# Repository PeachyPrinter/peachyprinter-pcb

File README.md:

If you're looking for the version of the Peachy Printer that we were gearing up to manufacture, look at mini-v1.14. 

If you're wondering what v1.15 is all about, it's a work-in-progress that we started because of a huge panic: right around the time we were getting ready for our final test manufacturing run, the STM32F042 practically vanished from the entire supply chain! We couldn't find them anywhere! So I quickly started redoing the board to use an STM32F070 instead, but in the end the supply chain recovered before we had to pull the trigger on the respin.

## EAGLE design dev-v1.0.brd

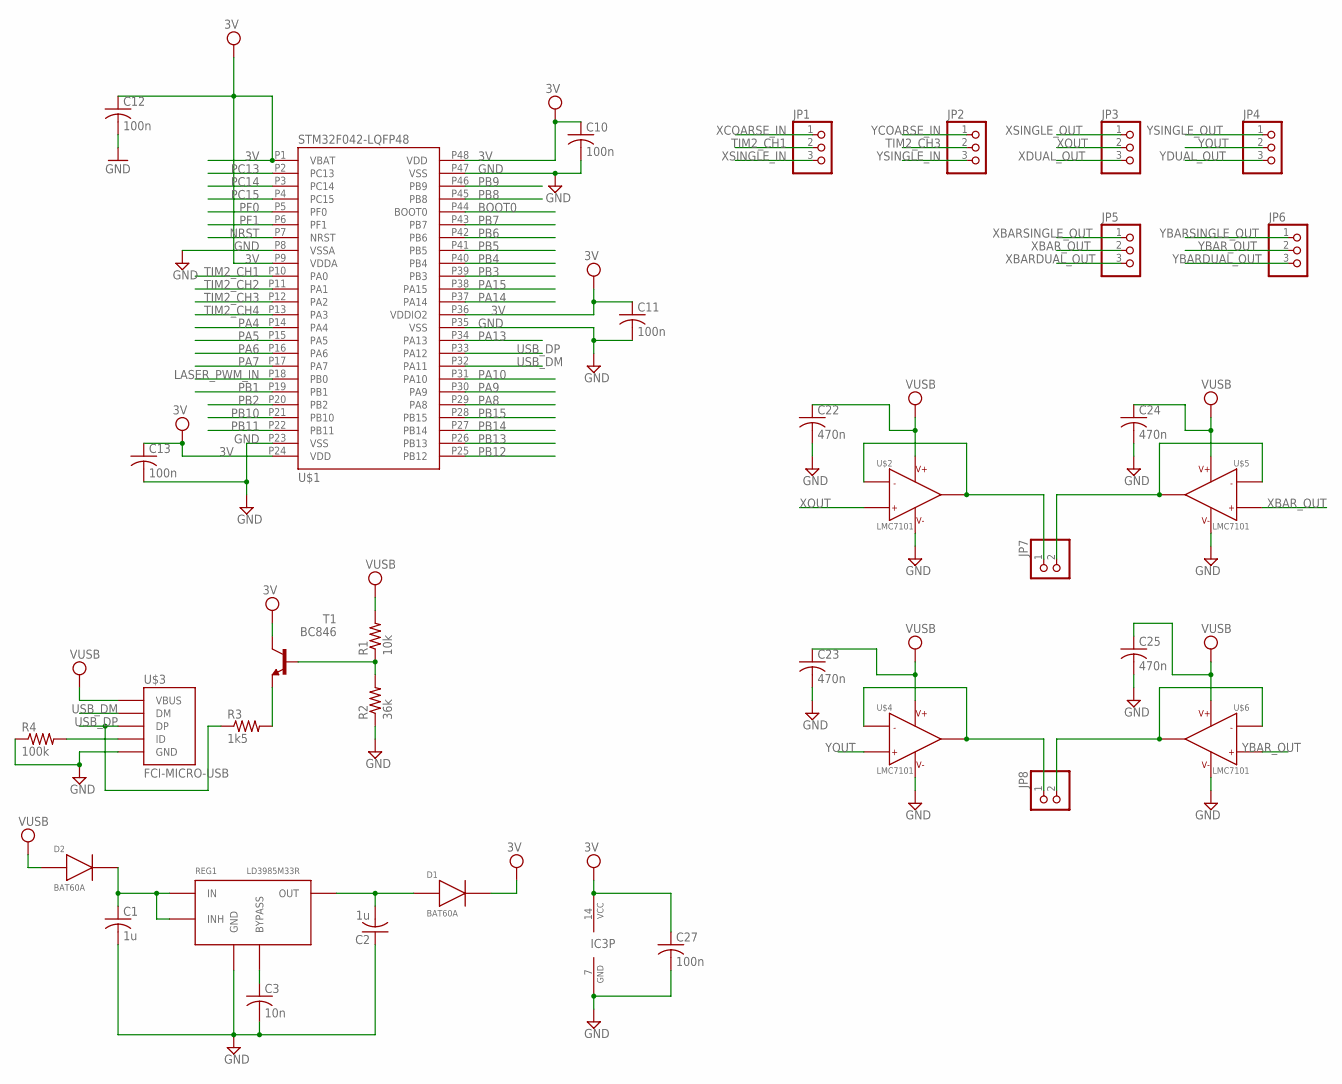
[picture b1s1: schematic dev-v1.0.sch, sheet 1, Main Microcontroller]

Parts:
C1, C2: 1u; C0603
C3: 10n; C0603
C10, C11, C12, C13, C27: 100n; C0603
C22, C23, C24, C25: 470n; C0603
D1, D2: BAT60A; SOD323
IC3: 74S04D; SO14
JP1, JP2, JP3, JP4, JP5, JP6: PINHD-1X3; 1X03
JP7, JP8: PINHD-1X2; 1X02
R1: 10k; R0603
R2: 36k; R0603
R3: 1k5; R0603
R4: 100k; R0603
REG1: LD3985M33R; SOT23-5L
T1: BC846; SOT23
U$1: STM32F042-LQFP48; LQFP48
U$2, U$4, U$5, U$6: LMC7101; SOT23-5
U$3: FCI-MICRO-USB; FCI-MICROUSB

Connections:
3V: C10.1, C11.1, C12.1, C13.1, C27.1, D1.1, IC3.14 (VCC), T1.3 (C), U$1.P1 (VBAT), U$1.P9 (VDDA), U$1.P24 (VDD), U$1.P36 (VDDIO2), U$1.P48 (VDD); also elsewhere on the board
3V3: C2.2, D1.2, REG1.OUT
BOOT0: U$1.P44 (BOOT0); also elsewhere on the board
GND: C1.2, C2.1, C3.2, C10.2, C11.2, C12.2, C13.2, C22.2, C23.2, C24.2, C25.2, C27.2, IC3.7 (GND), R2.1, R4.1, REG1.GND, U$1.P8 (VSSA), U$1.P23 (VSS), U$1.P35 (VSS), U$1.P47 (VSS), U$2.5, U$3.P5 (GND), U$4.5, U$5.5, U$6.5; also elsewhere on the board
LASER_PWM_IN: U$1.P18 (PB0); also elsewhere on the board
unnamed: C3.1, REG1.BYPASS
unnamed: R1.1, R2.2, T1.1 (B)
unnamed: R3.2, T1.2 (E)
unnamed: C1.1, D2.1, REG1.IN, REG1.INHIBIT (INH)
unnamed: R4.2, U$3.P4 (ID)
unnamed: JP7.1, U$2.1, U$2.4
unnamed: JP8.1, U$4.1, U$4.4
unnamed: JP7.2, U$5.1, U$5.4
unnamed: JP8.2, U$6.1, U$6.4
NRST: U$1.P7 (NRST); also elsewhere on the board
PA4: U$1.P14 (PA4); also elsewhere on the board
PA5: U$1.P15 (PA5); also elsewhere on the board
PA6: U$1.P16 (PA6); also elsewhere on the board
PA7: U$1.P17 (PA7); also elsewhere on the board
PA8: U$1.P29 (PA8); also elsewhere on the board
PA9: U$1.P30 (PA9); also elsewhere on the board
PA10: U$1.P31 (PA10); also elsewhere on the board
PA13: U$1.P34 (PA13); also elsewhere on the board
PA14: U$1.P37 (PA14); also elsewhere on the board
PA15: U$1.P38 (PA15); also elsewhere on the board
PB1: U$1.P19 (PB1); also elsewhere on the board
PB2: U$1.P20 (PB2); also elsewhere on the board
PB3: U$1.P39 (PB3); also elsewhere on the board
PB4: U$1.P40 (PB4); also elsewhere on the board
PB5: U$1.P41 (PB5); also elsewhere on the board
PB6: U$1.P42 (PB6); also elsewhere on the board
PB7: U$1.P43 (PB7); also elsewhere on the board
PB8: U$1.P45 (PB8); also elsewhere on the board
PB9: U$1.P46 (PB9); also elsewhere on the board
PB10: U$1.P21 (PB10); also elsewhere on the board
PB11: U$1.P22 (PB11); also elsewhere on the board
PB12: U$1.P25 (PB12); also elsewhere on the board
PB13: U$1.P26 (PB13); also elsewhere on the board
PB14: U$1.P27 (PB14); also elsewhere on the board
PB15: U$1.P28 (PB15); also elsewhere on the board
PC13: U$1.P2 (PC13); also elsewhere on the board
PC14: U$1.P3 (PC14); also elsewhere on the board
PC15: U$1.P4 (PC15); also elsewhere on the board
PF0: U$1.P5 (PF0); also elsewhere on the board
PF1: U$1.P6 (PF1); also elsewhere on the board
TIM2_CH1: JP1.2, U$1.P10 (PA0); also elsewhere on the board
TIM2_CH2: U$1.P11 (PA1); also elsewhere on the board
TIM2_CH3: JP2.2, U$1.P12 (PA2); also elsewhere on the board
TIM2_CH4: U$1.P13 (PA3); also elsewhere on the board
USB_DM: U$1.P32 (PA11), U$3.P2 (DM); also elsewhere on the board
USB_DP: R3.1, U$1.P33 (PA12), U$3.P3 (DP); also elsewhere on the board
VUSB: C22.1, C23.1, C24.1, C25.1, D2.2, R1.2, U$2.2, U$3.P1 (VBUS), U$4.2, U$5.2, U$6.2; also elsewhere on the board
XBARDUAL_OUT: JP5.3; also elsewhere on the board
XBARSINGLE_OUT: JP5.1; also elsewhere on the board
XBAR_OUT: JP5.2, U$5.3
XCOARSE_IN: JP1.1; also elsewhere on the board
XDUAL_OUT: JP3.3; also elsewhere on the board
XOUT: JP3.2, U$2.3
XSINGLE_IN: JP1.3; also elsewhere on the board
XSINGLE_OUT: JP3.1; also elsewhere on the board
YBARDUAL_OUT: JP6.3; also elsewhere on the board
YBARSINGLE_OUT: JP6.1; also elsewhere on the board
YBAR_OUT: JP6.2, U$6.3
YCOARSE_IN: JP2.1; also elsewhere on the board
YDUAL_OUT: JP4.3; also elsewhere on the board
YOUT: JP4.2, U$4.3
YSINGLE_IN: JP2.3; also elsewhere on the board
YSINGLE_OUT: JP4.1; also elsewhere on the board

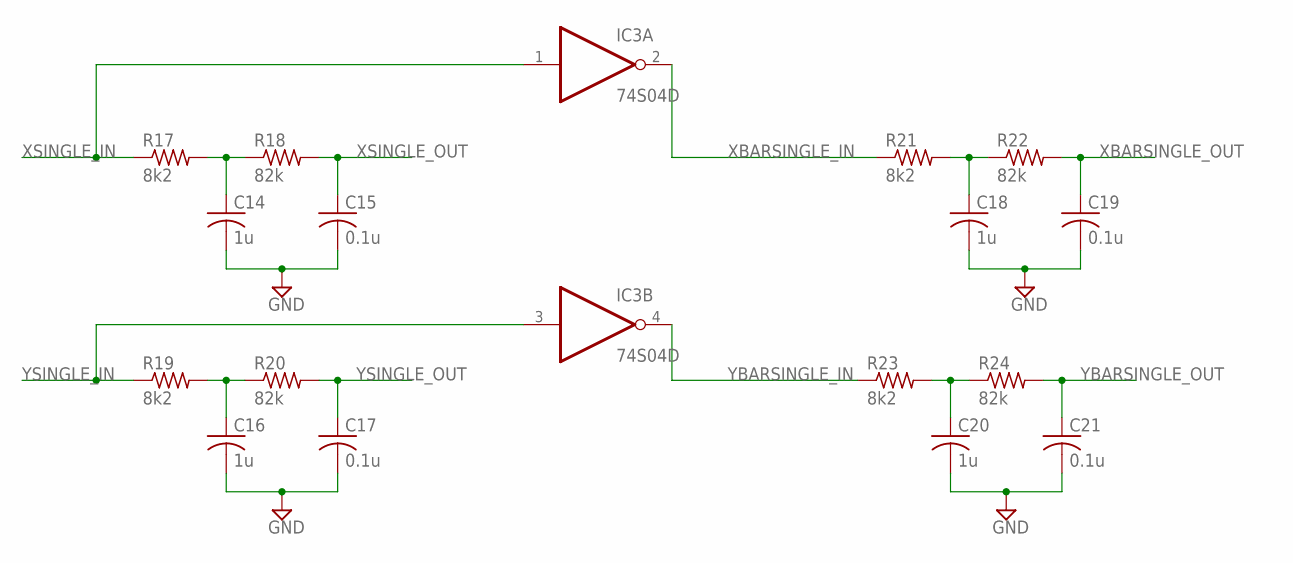
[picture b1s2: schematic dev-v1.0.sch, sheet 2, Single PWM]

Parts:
C14, C16, C18, C20: 1u; C0603
C15, C17, C19, C21: 0.1u; C0603
IC3: 74S04D; SO14
R17, R19, R21, R23: 8k2; R0603
R18, R20, R22, R24: 82k; R0603

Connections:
GND: C14.2, C15.2, C16.2, C17.2, C18.2, C19.2, C20.2, C21.2; also elsewhere on the board
unnamed: C14.1, R17.2, R18.1
unnamed: C16.1, R19.2, R20.1
unnamed: C18.1, R21.2, R22.1
unnamed: C20.1, R23.2, R24.1
XBARSINGLE_IN: IC3.2 (O), R21.1
XBARSINGLE_OUT: C19.1, R22.2; also elsewhere on the board
XSINGLE_IN: IC3.1 (I), R17.1; also elsewhere on the board
XSINGLE_OUT: C15.1, R18.2; also elsewhere on the board
YBARSINGLE_IN: IC3.4 (O), R23.1
YBARSINGLE_OUT: C21.1, R24.2; also elsewhere on the board
YSINGLE_IN: IC3.3 (I), R19.1; also elsewhere on the board
YSINGLE_OUT: C17.1, R20.2; also elsewhere on the board

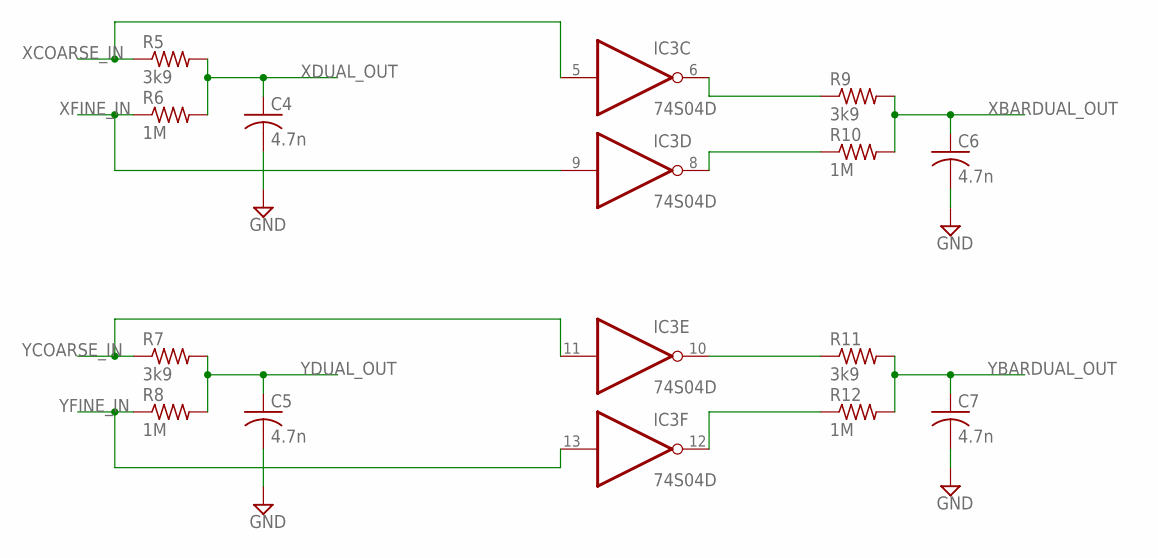
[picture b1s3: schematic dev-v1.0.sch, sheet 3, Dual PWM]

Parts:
C4, C5, C6, C7: 4.7n; C0603
IC3: 74S04D; SO14
R5, R7, R9, R11: 3k9; R0603
R6, R8, R10, R12: 1M; R0603

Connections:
GND: C4.2, C5.2, C6.2, C7.2; also elsewhere on the board
unnamed: IC3.10 (O), R11.1
unnamed: IC3.12 (O), R12.1
unnamed: IC3.8 (O), R10.1
unnamed: IC3.6 (O), R9.1
XBARDUAL_OUT: C6.1, R9.2, R10.2; also elsewhere on the board
XCOARSE_IN: IC3.5 (I), R5.1; also elsewhere on the board
XDUAL_OUT: C4.1, R5.2, R6.2; also elsewhere on the board
XFINE_IN: IC3.9 (I), R6.1
YBARDUAL_OUT: C7.1, R11.2, R12.2; also elsewhere on the board
YCOARSE_IN: IC3.11 (I), R7.1; also elsewhere on the board
YDUAL_OUT: C5.1, R7.2, R8.2; also elsewhere on the board
YFINE_IN: IC3.13 (I), R8.1

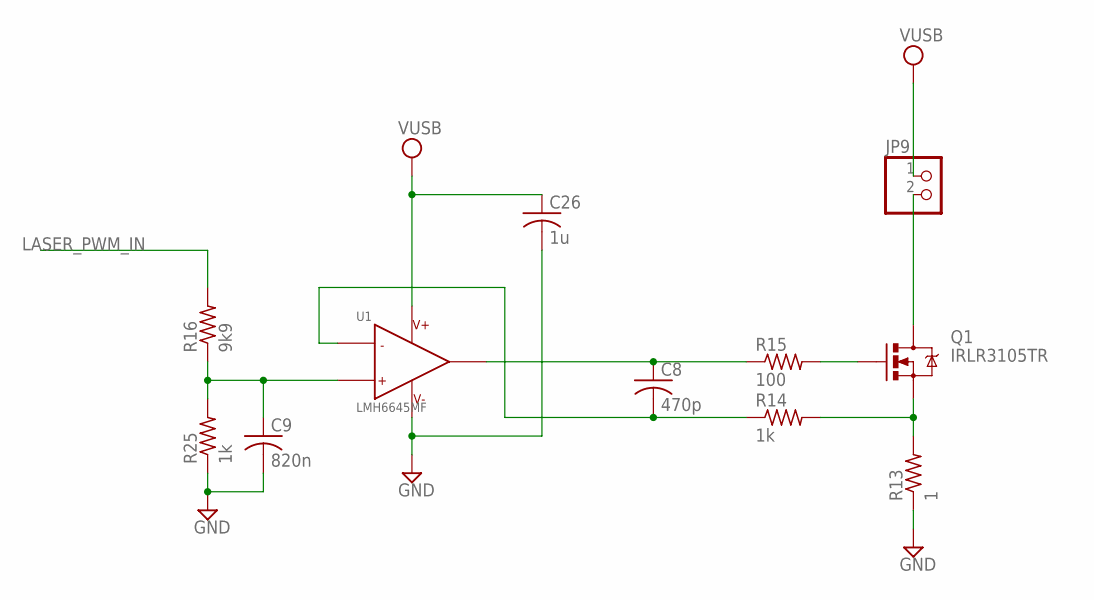
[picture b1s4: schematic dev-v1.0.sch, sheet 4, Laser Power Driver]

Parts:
C8: 470p; C0603
C9: 820n; C0603
C26: 1u; C0603
JP9: PINHD-1X2; 1X02
Q1: IRLR3105TR; DPAK
R13: 1; R0603
R14, R25: 1k; R0603
R15: 100; R0603
R16: 9k9; R0603
U1: LMH6645MF; SOT23-5

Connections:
GND: C9.2, C26.2, R13.1, R25.1, U1.2 (V-); also elsewhere on the board
LASER_PWM_IN: R16.2; also elsewhere on the board
unnamed: JP9.2, Q1.4 (D)
unnamed: Q1.3 (S), R13.2, R14.2
unnamed: C8.2, R14.1, U1.4 (IN-)
unnamed: Q1.1 (G), R15.2
unnamed: C8.1, R15.1, U1.1 (OUT)
unnamed: C9.1, R16.1, R25.2, U1.3 (IN+)
VUSB: C26.1, JP9.1, U1.5 (V+); also elsewhere on the board

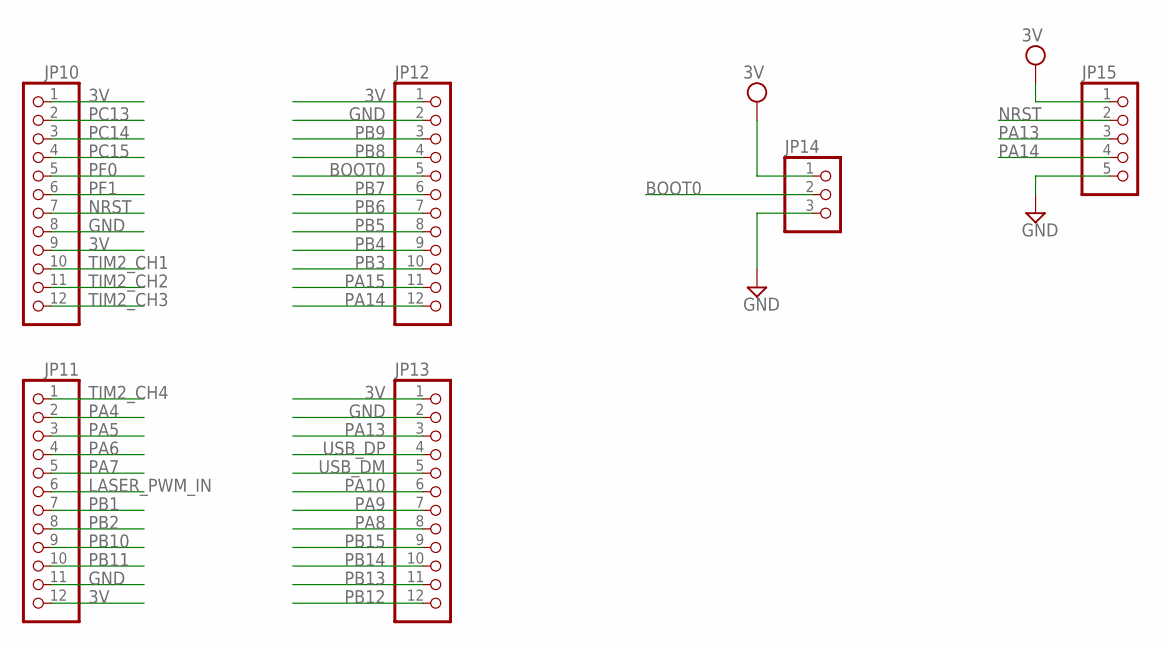
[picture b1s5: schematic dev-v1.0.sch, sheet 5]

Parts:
JP10, JP11, JP12, JP13: PINHD-1X12; 1X12
JP14: PINHD-1X3; 1X03
JP15: PINHD-1X5; 1X05

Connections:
3V: JP10.1, JP10.9, JP11.12, JP12.1, JP13.1, JP14.1, JP15.1; also elsewhere on the board
BOOT0: JP12.5, JP14.2; also elsewhere on the board
GND: JP10.8, JP11.11, JP12.2, JP13.2, JP14.3, JP15.5; also elsewhere on the board
LASER_PWM_IN: JP11.6; also elsewhere on the board
NRST: JP10.7, JP15.2; also elsewhere on the board
PA4: JP11.2; also elsewhere on the board
PA5: JP11.3; also elsewhere on the board
PA6: JP11.4; also elsewhere on the board
PA7: JP11.5; also elsewhere on the board
PA8: JP13.8; also elsewhere on the board
PA9: JP13.7; also elsewhere on the board
PA10: JP13.6; also elsewhere on the board
PA13: JP13.3, JP15.3; also elsewhere on the board
PA14: JP12.12, JP15.4; also elsewhere on the board
PA15: JP12.11; also elsewhere on the board
PB1: JP11.7; also elsewhere on the board
PB2: JP11.8; also elsewhere on the board
PB3: JP12.10; also elsewhere on the board
PB4: JP12.9; also elsewhere on the board
PB5: JP12.8; also elsewhere on the board
PB6: JP12.7; also elsewhere on the board
PB7: JP12.6; also elsewhere on the board
PB8: JP12.4; also elsewhere on the board
PB9: JP12.3; also elsewhere on the board
PB10: JP11.9; also elsewhere on the board
PB11: JP11.10; also elsewhere on the board
PB12: JP13.12; also elsewhere on the board
PB13: JP13.11; also elsewhere on the board
PB14: JP13.10; also elsewhere on the board
PB15: JP13.9; also elsewhere on the board
PC13: JP10.2; also elsewhere on the board
PC14: JP10.3; also elsewhere on the board
PC15: JP10.4; also elsewhere on the board
PF0: JP10.5; also elsewhere on the board
PF1: JP10.6; also elsewhere on the board
TIM2_CH1: JP10.10; also elsewhere on the board
TIM2_CH2: JP10.11; also elsewhere on the board
TIM2_CH3: JP10.12; also elsewhere on the board
TIM2_CH4: JP11.1; also elsewhere on the board
USB_DM: JP13.5; also elsewhere on the board
USB_DP: JP13.4; also elsewhere on the board

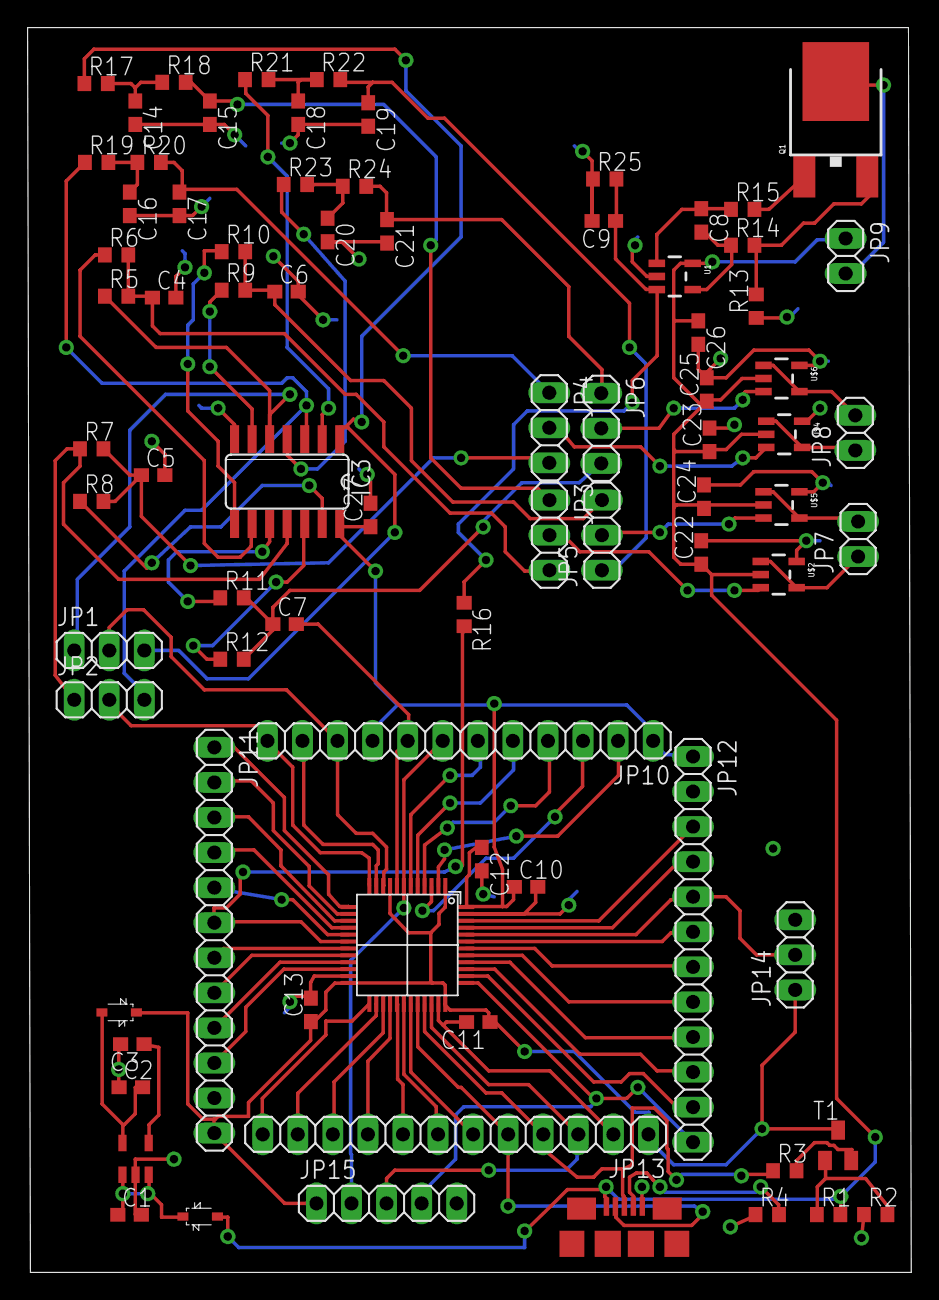
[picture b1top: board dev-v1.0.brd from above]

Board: 2 copper layers, 64.0 x 90.2 mm, 80 parts (0 on the bottom side), 86 nets.

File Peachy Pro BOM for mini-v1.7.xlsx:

Value | Device | Package | Digikey Part | Newark Part Number | Unit Price | /1000 price | QTY | Single Price | Vol Price | QTY +15%
100n | C-USC0603 | C0603 | 399-1095-1-ND |  | 0.13 | 8.1600000000000006E-3 | 5 | 0.65 | 4.0800000000000003E-2 | 58
10n | C-USC0603 | C0603 | 399-8988-1-ND |  | 0.32 | 6.9339999999999999E-2 | 1 | 0.32 | 6.9339999999999999E-2 | 12
10uF | C-USC0603 | C0603 | 490-10475-1-ND |  | 0.27 | 5.0560000000000001E-2 | 1 | 0.27 | 5.0560000000000001E-2 | 12
1u | C-USC0603 | C0603 | 587-1242-1-ND |  | 0.13 | 1.321E-2 | 3 | 0.39 | 3.9629999999999999E-2 | 35
2.2u | C-USC0603 | C0603 | 587-2983-1-ND |  | 0.22 | 4.095E-2 | 1 | 0.22 | 4.095E-2 | 12
4.7n | C-USC0603 | C0603 | 399-1087-1-ND |  | 0.13 | 9.7099999999999999E-3 | 4 | 0.52 | 3.884E-2 | 46
470n | C-USC0603 | C0603 | 587-1252-1-ND |  | 0.13 | 2.1360000000000001E-2 | 4 | 0.52 | 8.5440000000000002E-2 | 46
470p | C-USC0603 | C0603 | 399-1075-1-ND |  | 0.13 | 1.3979999999999999E-2 | 1 | 0.13 | 1.3979999999999999E-2 | 12
560pF/50V | C-USC0603 | C0603 | 399-1076-1-ND |  | 0.32 | 7.911E-2 | 1 | 0.32 | 7.911E-2 | 12
820n | C-USC0603 | C0603 | 399-3117-1-ND |  | 0.34 | 8.2159999999999997E-2 | 1 | 0.34 | 8.2159999999999997E-2 | 12
BAT60A | BAT60A | SOD323 | BAT60AE6327INCT-ND |  | 0.71 | 0.14888000000000001 | 2 | 1.42 | 0.29776000000000002 | 23
74S04D | 74S04D | SO14 | 568-1384-1-ND |  | 0.63 | 0.13336000000000001 | 1 | 0.63 | 0.13336000000000001 | 12
 | LEDCHIP-LED0603 | CHIP-LED0603 | 475-2512-1-ND |  | 0.12 | 6.0859999999999997E-2 | 4 | 0.48 | 0.24343999999999999 | 46
IRLR3105TR | FET-N-IRLR3105TRIRLR3105TR | DPAK | IRLR3105TRPBFCT-ND |  | 1.48 | 0.55349999999999999 | 1 | 1.48 | 0.55349999999999999 | 12
1 | R-US_R0603 | R0603 | 541-1.00HHCT-ND |  | 0.112 | 2.359E-2 | 1 | 0.112 | 2.359E-2 | 12
100 | R-US_R0603 | R0603 | 541-100HCT-ND |  | 0.112 | 2.359E-2 | 1 | 0.112 | 2.359E-2 | 12
100k | R-US_R0603 | R0603 | 541-100KHCT-ND |  | 0.112 | 2.359E-2 | 1 | 0.112 | 2.359E-2 | 12
10k | R-US_R0603 | R0603 | 541-10.0KHCT-ND |  | 0.112 | 2.359E-2 | 1 | 0.112 | 2.359E-2 | 12
13k3 | R-US_R0603 | R0603 | 541-13.3KHCT-ND |  | 0.112 | 2.359E-2 | 1 | 0.112 | 2.359E-2 | 12
1k | R-US_R0603 | R0603 | 541-1.00KHCT-ND |  | 0.112 | 2.359E-2 | 2 | 0.224 | 4.718E-2 | 23
1M | R-US_R0603 | R0603 | 541-1.00MHCT-ND |  | 0.112 | 2.359E-2 | 5 | 0.56000000000000005 | 0.11795 | 58
3k9 | R-US_R0603 | R0603 | 541-3.90KHCT-ND |  | 0.112 | 2.359E-2 | 4 | 0.44800000000000001 | 9.4359999999999999E-2 | 46
52k3 | R-US_R0603 | R0603 | 541-52.3KHCT-ND |  | 0.112 | 2.359E-2 | 1 | 0.112 | 2.359E-2 | 12
9k9 | R-US_R0603 | R0603 | 541-9.09KHCT-N |  | 0.112 | 2.359E-2 | 1 | 0.112 | 2.359E-2 | 12
LD3985M33R | LD3985MXXR | SOT23-5L | 497-3504-1-ND |  | 0.96 | 0.33534999999999998 | 1 | 0.96 | 0.33534999999999998 | 12
 | R-US_R0603 | R0603 | 541-1.00KHCT-ND |  | 0.112 | 2.359E-2 | 4 | 0.44800000000000001 | 9.4359999999999999E-2 | 46
FCI-MICRO-USB | FCI-MICRO-USB | FCI-MICROUSB | 609-4613-1-ND |  | 0.6 | 0.33650000000000002 | 1 | 0.6 | 0.33650000000000002 | 12
LMC7101 | LMC7101 | SOT23-5 | 576-2575-1-ND |  | 0.98 | 0.38900000000000001 | 4 | 3.92 | 1.556 | 46
LMH6645MF | OPAMP-SINGLELMH6645MF | SOT23-5 | LMH6645MF/NOPBCT-ND |  | 2.4900000000000002 | 0.97596000000000005 | 1 | 2.4900000000000002 | 0.97596000000000005 | 12
LMR62014 | LMR62014 | SOT23-5 | LMR62014XMF/NOPBCT-ND |  | 2.3199999999999998 | 0.80115999999999998 | 1 | 2.3199999999999998 | 0.80115999999999998 | 12
MBR0520 | MBR0520 | SOD123 | MBR0520LT1GOSCT-ND | 48K7498 | 0.40699999999999997 | 7.5999999999999998E-2 | 3 | 1.2209999999999999 | 0.22799999999999998 | 35
SDR0403-100ML | SDR0403 | SDR0403 | SDR0403-100MLCT-ND |  | 0.65 | 0.31546999999999997 | 1 | 0.65 | 0.31546999999999997 | 12
SP3002 | SP3002 | SC70-6 | F2916CT-ND |  | 0.96 | 0.38456000000000001 | 2 | 1.92 | 0.76912000000000003 | 23
STM32F042-LQFP48 | STM32F042-LQFP48 | LQFP48 | 497-14648-ND |  | 4.08 | 2.0411199999999998 | 1 | 4.08 | 2.0411199999999998 | 12
 | L_TDK_1005 | MLK1005 | 445-1565-1-ND |  | 0.13 | 3.5180000000000003E-2 | 1 | 0.13 | 3.5180000000000003E-2 | 12
 | NOTE: Replace the existing one with this one (0603)
 |  |  |  |  |  |  | 68 | 28.444999999999997 | 9.6817100000000007

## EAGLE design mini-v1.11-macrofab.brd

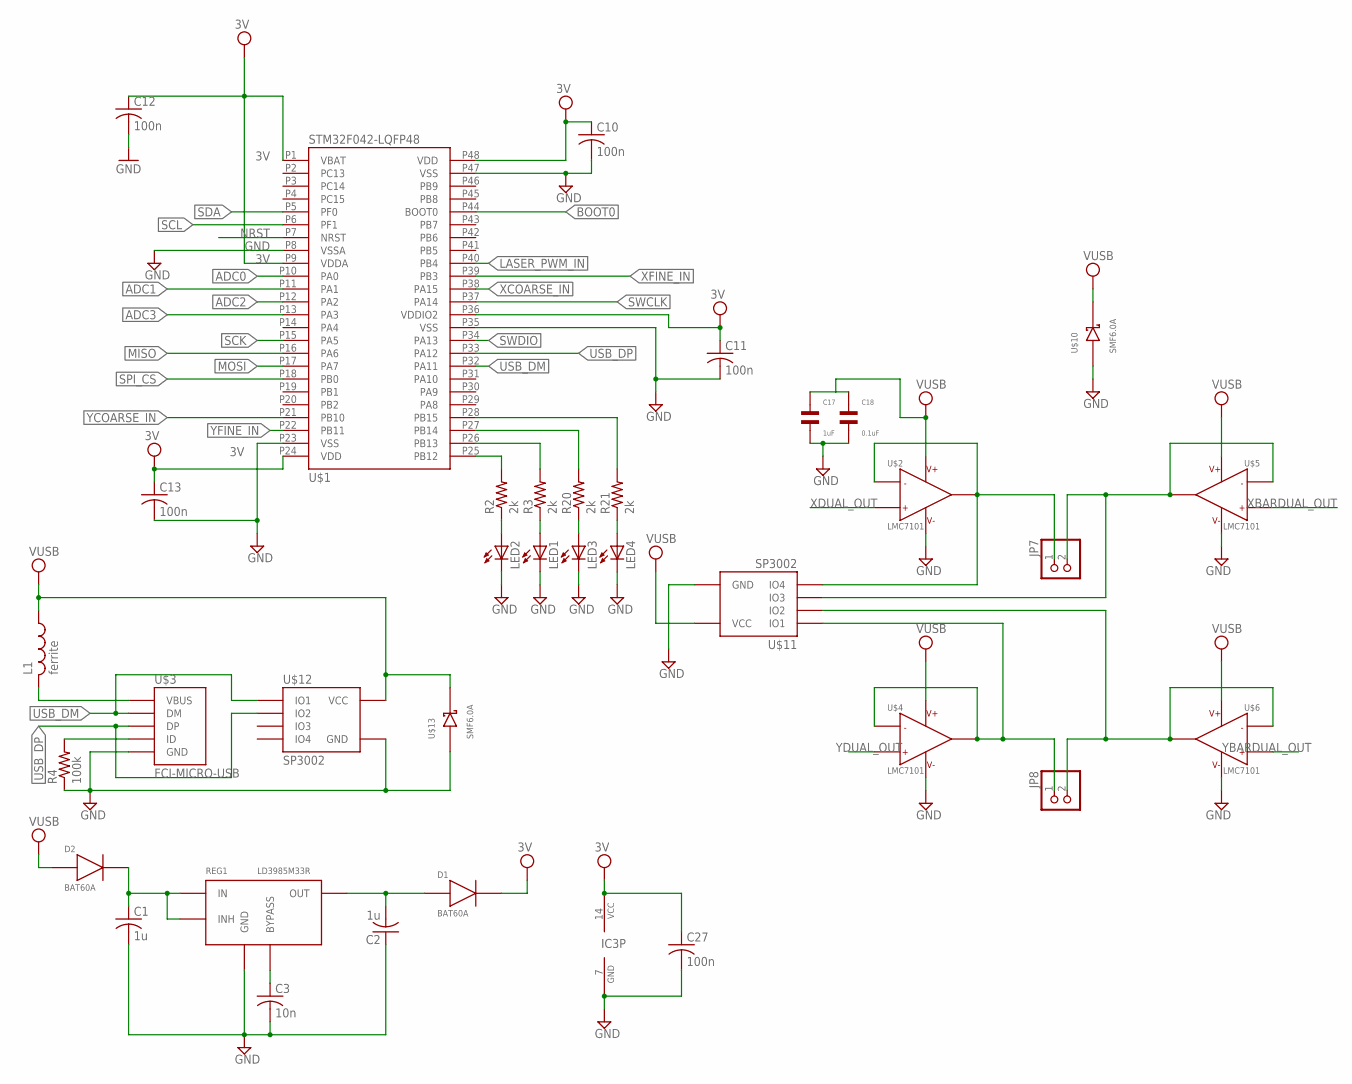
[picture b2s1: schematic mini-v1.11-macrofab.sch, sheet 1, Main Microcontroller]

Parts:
C1, C2: 1u; C0603
C3: 10n; C0603
C10, C11, C12, C13, C27: 100n; C0603
C17: 1uF; C0603
C18: 0.1uF; C0603
D1, D2: BAT60A; SOD323
IC3: 74S04D; SO14
JP7, JP8: PINHD-1X2; 1X02
L1: ferrite; C0603
LED1, LED2, LED3, LED4: LEDCHIP-LED0603; CHIP-LED0603
R2, R3, R20, R21: 2k; R0603
R4: 100k; R0603
REG1: LD3985M33R; SOT23-5L
U$1: STM32F042-LQFP48; LQFP48
U$2, U$4, U$5, U$6: LMC7101; SOT23-5
U$3: FCI-MICRO-USB; FCI-MICROUSB
U$10, U$13: SMF6.0A; SOD123
U$11, U$12: SP3002; SC70-6

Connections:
3V: C10.1, C11.1, C12.1, C13.1, C27.1, D1.1, IC3.14 (VCC), U$1.P1 (VBAT), U$1.P9 (VDDA), U$1.P24 (VDD), U$1.P36 (VDDIO2), U$1.P48 (VDD); also elsewhere on the board
3V3: C2.2, D1.2, REG1.OUT
ADC0: U$1.P10 (PA0); also elsewhere on the board
ADC1: U$1.P11 (PA1); also elsewhere on the board
ADC2: U$1.P12 (PA2); also elsewhere on the board
ADC3: U$1.P13 (PA3); also elsewhere on the board
BOOT0: U$1.P44 (BOOT0); also elsewhere on the board
GND: C1.2, C2.1, C3.2, C10.2, C11.2, C12.2, C13.2, C17.P$2, C18.P$2, C27.2, IC3.7 (GND), LED1.C, LED2.C, LED3.C, LED4.C, R4.1, REG1.GND, U$1.P8 (VSSA), U$1.P23 (VSS), U$1.P35 (VSS), U$1.P47 (VSS), U$2.5, U$3.P5 (GND), U$4.5, U$5.5, U$6.5, U$10.ANODE, U$11.P2 (GND), U$12.P2 (GND), U$13.ANODE; also elsewhere on the board
LASER_PWM_IN: U$1.P40 (PB4); also elsewhere on the board
MISO: U$1.P16 (PA6); also elsewhere on the board
MOSI: U$1.P17 (PA7); also elsewhere on the board
unnamed: C3.1, REG1.BYPASS
unnamed: R2.2, U$1.P25 (PB12)
unnamed: LED2.A, R2.1
unnamed: C1.1, D2.1, REG1.IN, REG1.INHIBIT (INH)
unnamed: R4.2, U$3.P4 (ID)
unnamed: JP7.1, U$2.1, U$2.4, U$11.P6 (IO4)
unnamed: JP8.1, U$4.1, U$4.4, U$11.P1 (IO1)
unnamed: LED1.A, R3.1
unnamed: R3.2, U$1.P26 (PB13)
unnamed: L1.2, U$3.P1 (VBUS)
unnamed: JP7.2, U$5.1, U$5.4, U$11.P4 (IO3)
unnamed: JP8.2, U$6.1, U$6.4, U$11.P3 (IO2)
unnamed: LED3.A, R20.1
unnamed: LED4.A, R21.1
unnamed: R20.2, U$1.P27 (PB14)
unnamed: R21.2, U$1.P28 (PB15)
NRST: U$1.P7 (NRST); also elsewhere on the board
SCK: U$1.P15 (PA5); also elsewhere on the board
SCL: U$1.P6 (PF1); also elsewhere on the board
SDA: U$1.P5 (PF0); also elsewhere on the board
SPI_CS: U$1.P18 (PB0); also elsewhere on the board
SWCLK: U$1.P37 (PA14); also elsewhere on the board
SWDIO: U$1.P34 (PA13); also elsewhere on the board
USB_DM: U$1.P32 (PA11), U$3.P2 (DM), U$12.P1 (IO1)
USB_DP: U$1.P33 (PA12), U$3.P3 (DP), U$12.P3 (IO2)
VUSB: C17.P$1, C18.P$1, D2.2, L1.1, U$2.2, U$4.2, U$5.2, U$6.2, U$10.CATHODE, U$11.P5 (VCC), U$12.P5 (VCC), U$13.CATHODE; also elsewhere on the board
XBARDUAL_OUT: U$5.3; also elsewhere on the board
XCOARSE_IN: U$1.P38 (PA15); also elsewhere on the board
XDUAL_OUT: U$2.3; also elsewhere on the board
XFINE_IN: U$1.P39 (PB3); also elsewhere on the board
YBARDUAL_OUT: U$6.3; also elsewhere on the board
YCOARSE_IN: U$1.P21 (PB10); also elsewhere on the board
YDUAL_OUT: U$4.3; also elsewhere on the board
YFINE_IN: U$1.P22 (PB11); also elsewhere on the board

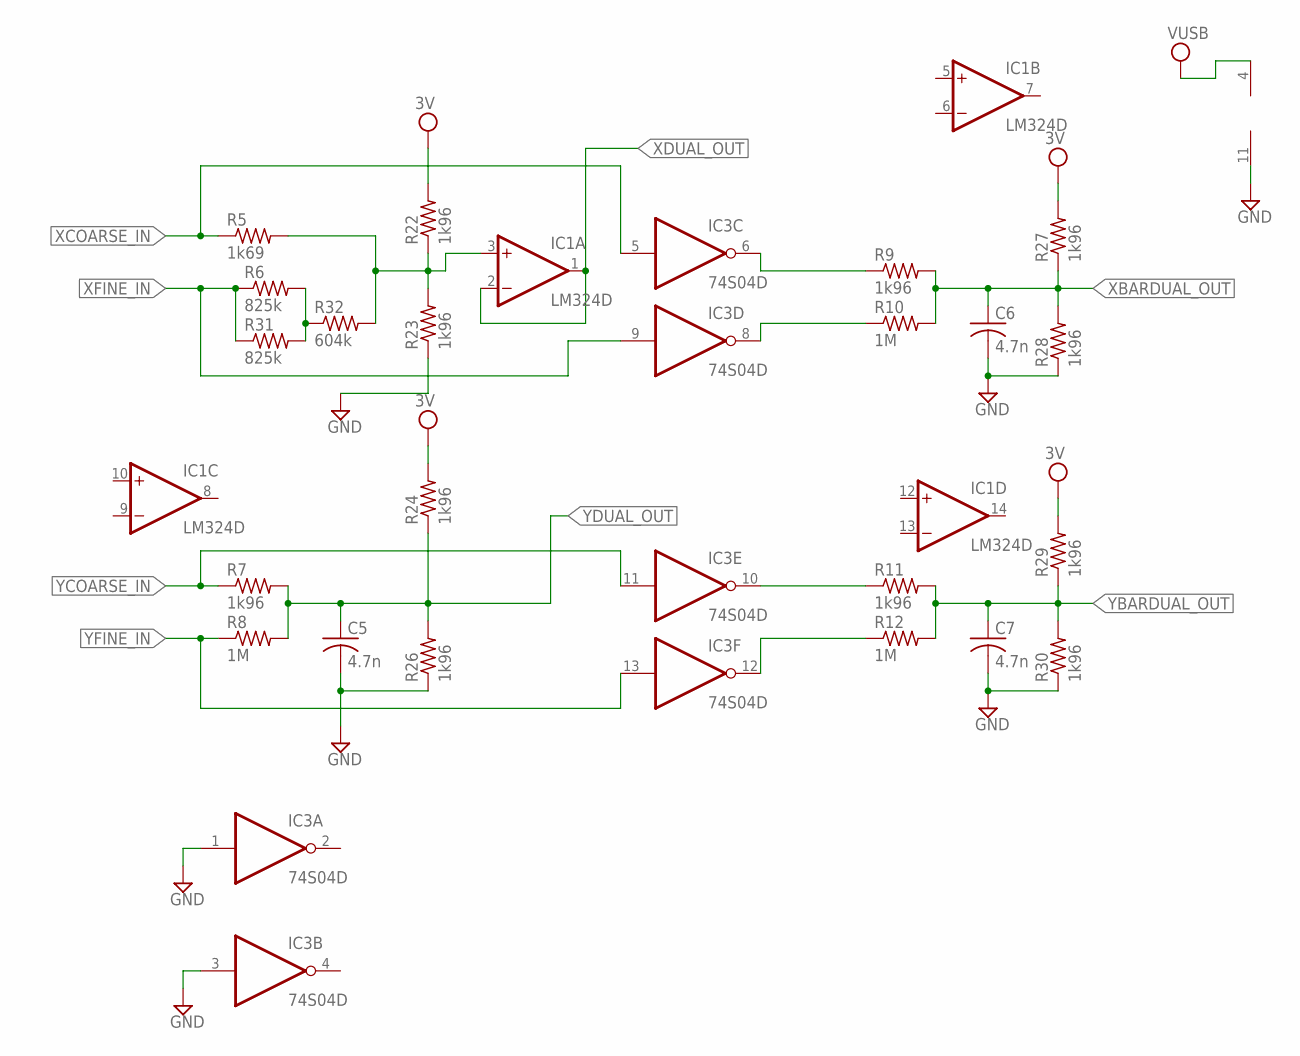
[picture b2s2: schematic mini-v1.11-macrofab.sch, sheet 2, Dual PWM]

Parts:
C5, C6, C7: 4.7n; C0603
IC1: LM324D; SO14
IC3: 74S04D; SO14
R5: 1k69; R0603
R6, R31: 825k; R0603
R7, R9, R11, R22, R23, R24, R26, R27, R28, R29, R30: 1k96; R0603
R8, R10, R12: 1M; R0603
R32: 604k; R0603

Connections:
3V: R22.2, R24.2, R27.2, R29.2; also elsewhere on the board
GND: C5.2, C6.2, C7.2, IC1.11 (V-), IC3.1 (I), IC3.3 (I), R23.1, R26.1, R28.1, R30.1; also elsewhere on the board
unnamed: IC3.10 (O), R11.1
unnamed: IC3.12 (O), R12.1
unnamed: IC3.8 (O), R10.1
unnamed: IC3.6 (O), R9.1
unnamed: R6.2, R31.2, R32.1
unnamed: IC1.3 (+IN), R5.2, R22.1, R23.2, R32.2
VUSB: IC1.4 (V+); also elsewhere on the board
XBARDUAL_OUT: C6.1, R9.2, R10.2, R27.1, R28.2; also elsewhere on the board
XCOARSE_IN: IC3.5 (I), R5.1; also elsewhere on the board
XDUAL_OUT: IC1.1 (OUT), IC1.2 (-IN); also elsewhere on the board
XFINE_IN: IC3.9 (I), R6.1, R31.1; also elsewhere on the board
YBARDUAL_OUT: C7.1, R11.2, R12.2, R29.1, R30.2; also elsewhere on the board
YCOARSE_IN: IC3.11 (I), R7.1; also elsewhere on the board
YDUAL_OUT: C5.1, R7.2, R8.2, R24.1, R26.2; also elsewhere on the board
YFINE_IN: IC3.13 (I), R8.1; also elsewhere on the board

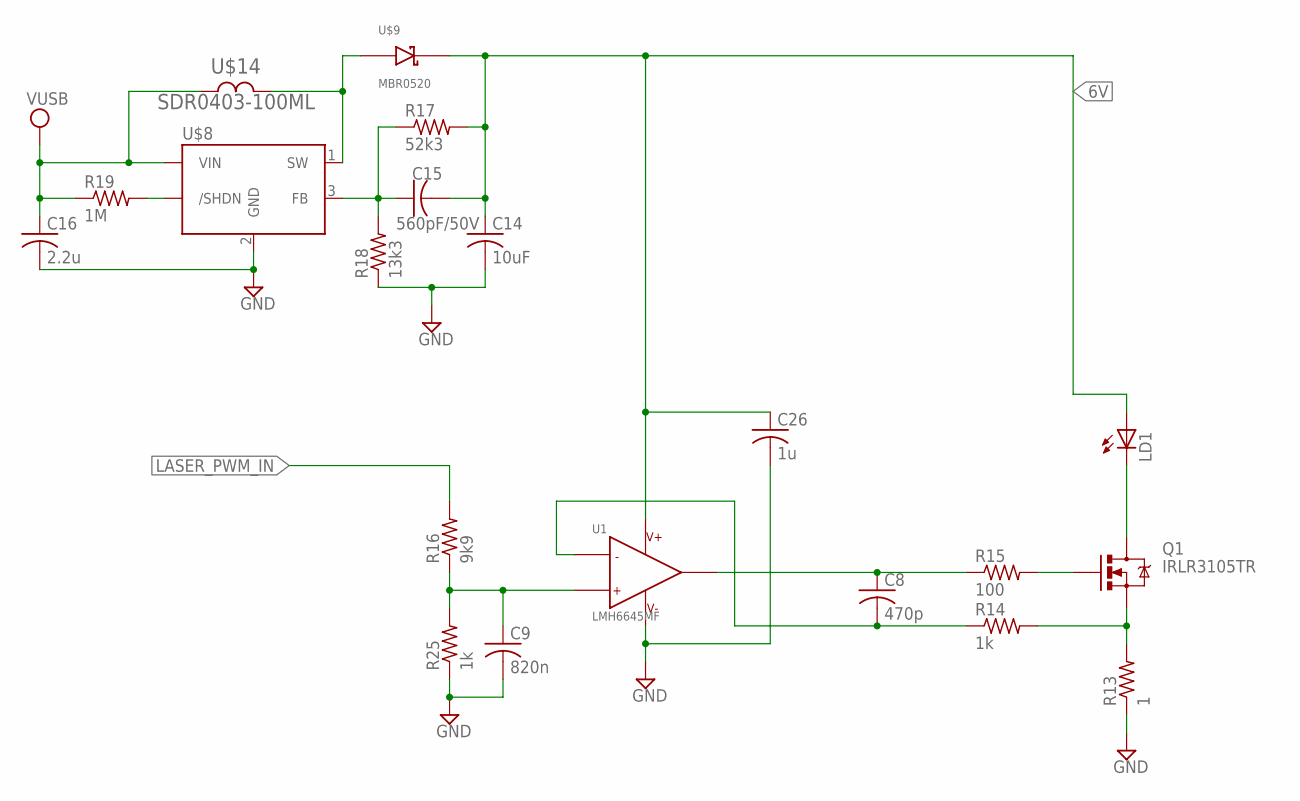
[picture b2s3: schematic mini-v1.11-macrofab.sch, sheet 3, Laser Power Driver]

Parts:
C8: 470p; C0603
C9: 820n; C0603
C14: 10uF; C0603
C15: 560pF/50V; C0603
C16: 2.2u; C0603
C26: 1u; C0603
LD1: LASERDIODELD2; LASERDIODE2; MPN 3 x (0552-2-15-15-11-27-10-0)
Q1: IRLR3105TR; DPAK
R13: 1; R0603
R14, R25: 1k; R0603
R15: 100; R0603
R16: 9k9; R0603
R17: 52k3; R0603
R18: 13k3; R0603
R19: 1M; R0603
U1: LMH6645MF; SOT23-5
U$8: LMR62014; SOT23-5
U$9: MBR0520; SOD123
U$14: SDR0403-100ML; SDR0403

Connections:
6V: C14.1, C15.2, C26.1, LD1.P$1 (A), R17.2, U1.5 (V+), U$9.CATHODE
GND: C9.2, C14.2, C16.2, C26.2, R13.1, R18.1, R25.1, U1.2 (V-), U$8.2 (GND); also elsewhere on the board
LASER_PWM_IN: R16.2; also elsewhere on the board
unnamed: U$8.1 (SW), U$9.ANODE, U$14.P$2
unnamed: LD1.P$3 (C), Q1.4 (D)
unnamed: Q1.3 (S), R13.2, R14.2
unnamed: C8.2, R14.1, U1.4 (IN-)
unnamed: Q1.1 (G), R15.2
unnamed: C8.1, R15.1, U1.1 (OUT)
unnamed: C9.1, R16.1, R25.2, U1.3 (IN+)
unnamed: C15.1, R17.1, R18.2, U$8.3 (FB)
unnamed: R19.2, U$8.4 (/SHDN)
VUSB: C16.1, R19.1, U$8.5 (VIN), U$14.P$1; also elsewhere on the board

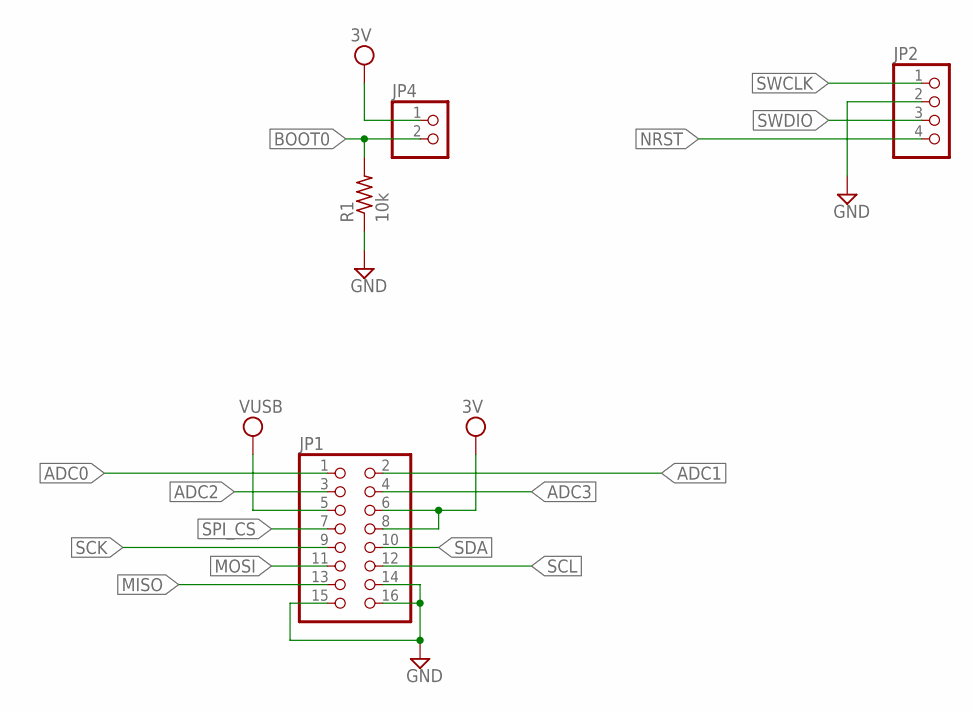
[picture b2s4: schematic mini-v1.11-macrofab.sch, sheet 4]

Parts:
JP1: PINHD-2X8; 2X08
JP2: PINHD-1X4; 1X04
JP4: PINHD-1X2; 1X02
R1: 10k; R0603

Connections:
3V: JP1.6, JP1.8, JP4.1; also elsewhere on the board
ADC0: JP1.1; also elsewhere on the board
ADC1: JP1.2; also elsewhere on the board
ADC2: JP1.3; also elsewhere on the board
ADC3: JP1.4; also elsewhere on the board
BOOT0: JP4.2, R1.2; also elsewhere on the board
GND: JP1.14, JP1.15, JP1.16, JP2.2, R1.1; also elsewhere on the board
MISO: JP1.13; also elsewhere on the board
MOSI: JP1.11; also elsewhere on the board
NRST: JP2.4; also elsewhere on the board
SCK: JP1.9; also elsewhere on the board
SCL: JP1.12; also elsewhere on the board
SDA: JP1.10; also elsewhere on the board
SPI_CS: JP1.7; also elsewhere on the board
SWCLK: JP2.1; also elsewhere on the board
SWDIO: JP2.3; also elsewhere on the board
VUSB: JP1.5; also elsewhere on the board

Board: 2 copper layers, 82 parts (0 on the bottom side), 61 nets, no tracks yet.

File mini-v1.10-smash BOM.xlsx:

Qty | Total Qty | Value | Device | Package | Digikey Part
1 | 15 | 10uF | C-USC0603 | C0603 | 490-10475-1-ND |  | Number of Boards | 15
1 | 15 | 560pF/50V | C-USC0603 | C0603 | 399-1076-1-ND |  | Breakage | 0
1 | 15 | 2.2u | C-USC0603 | C0603 | 587-2983-1-ND
1 | 15 | 10n | C-USC0603 | C0603 | 399-1091-1-ND
1 | 15 | 470p | C-USC0603 | C0603 | 399-1075-1-ND
1 | 15 | 820n | C-USC0603 | C0603 | 399-3117-1-ND
1 | 15 | 74S04D | 74S04D | SO14 | 568-1384-1-ND
1 | 15 | ferrite | L-US | C0603 | 445-1565-1-ND
1 | 15 | IRLR3105TR | FET-N-IRLR3105TRIRLR3105TR | DPAK | IRLR3105TRPBFCT-ND
1 | 15 | 10k | R-US_R0603 | R0603 | 541-10.0KHCT-ND
1 | 15 | 1 | R-US_R0603 | R0603 | 541-1.00HHCT-ND
1 | 15 | 100 | R-US_R0603 | R0603 | 541-100HCT-ND
1 | 15 | 9k9 | R-US_R0603 | R0603 | 541-9.09KHCT-ND
1 | 15 | 52k3 | R-US_R0603 | R0603 | 541-52.3KHCT-ND
1 | 15 | 13k3 | R-US_R0603 | R0603 | 541-13.3KHCT-ND
1 | 15 | 100k | R-US_R0603 | R0603 | 541-100KHCT-ND
1 | 15 | LD3985M33R | LD3985MXXR | SOT23-5L | LP3985IM5-3.3/NOPBCT-ND
1 | 15 | STM32F042-LQFP48 | STM32F042-LQFP48 | LQFP48 | 497-14648-ND
1 | 15 | SDR0403-100ML | SDR0403 | SDR0403 | SDR0403-100MLCT-ND
1 | 15 | FCI-MICRO-USB | FCI-MICRO-USB | FCI-MICROUSB | 609-4613-1-ND
1 | 15 | LMR62014 | LMR62014 | SOT23-5 | LMR62014XMF/NOPBCT-ND
1 | 15 | MBR0520 | MBR0520 | SOD123 | MBR0520LCT-ND
1 | 15 | LMH6645MF | OPAMP-SINGLELMH6645MF | SOT23-5 | LMH6645MF/NOPBCT-ND
2 | 30 | BAT60A | BAT60A | SOD323 | BAT60AE6327INCT-ND
2 | 30 | SMF6.0A | MBR0520 | SOD123 | F5749CT-ND
2 | 30 | SP3002 | SP3002 | SC70-6 | F2916CT-ND | Substituted
3 | 45 | 1u | C-USC0603 | C0603 | 587-1242-1-ND
4 | 60 | 470n | C-USC0603 | C0603 | 587-1252-1-ND
4 | 60 | 4.7n | C-USC0603 | C0603 | 399-1087-1-ND
4 | 60 |  | LEDCHIP-LED0603 | CHIP-LED0603 | 475-2512-1-ND
4 | 60 | LMC7101 | LMC7101 | SOT23-5 | 576-2575-1-ND
5 | 75 | 100n | C-USC0603 | C0603 | 399-1095-1-ND
5 | 75 | 1M | R-US_R0603 | R0603 | 541-1.00MHCT-ND
6 | 90 | 1k | R-US_R0603 | R0603 | 541-1.00KHCT-ND
12 | 180 | 1k96 | R-US_R0603 | R0603 | 541-1.96KHCT-ND
